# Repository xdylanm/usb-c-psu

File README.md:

# usb-c-psu
Notes for USB-C PSU design

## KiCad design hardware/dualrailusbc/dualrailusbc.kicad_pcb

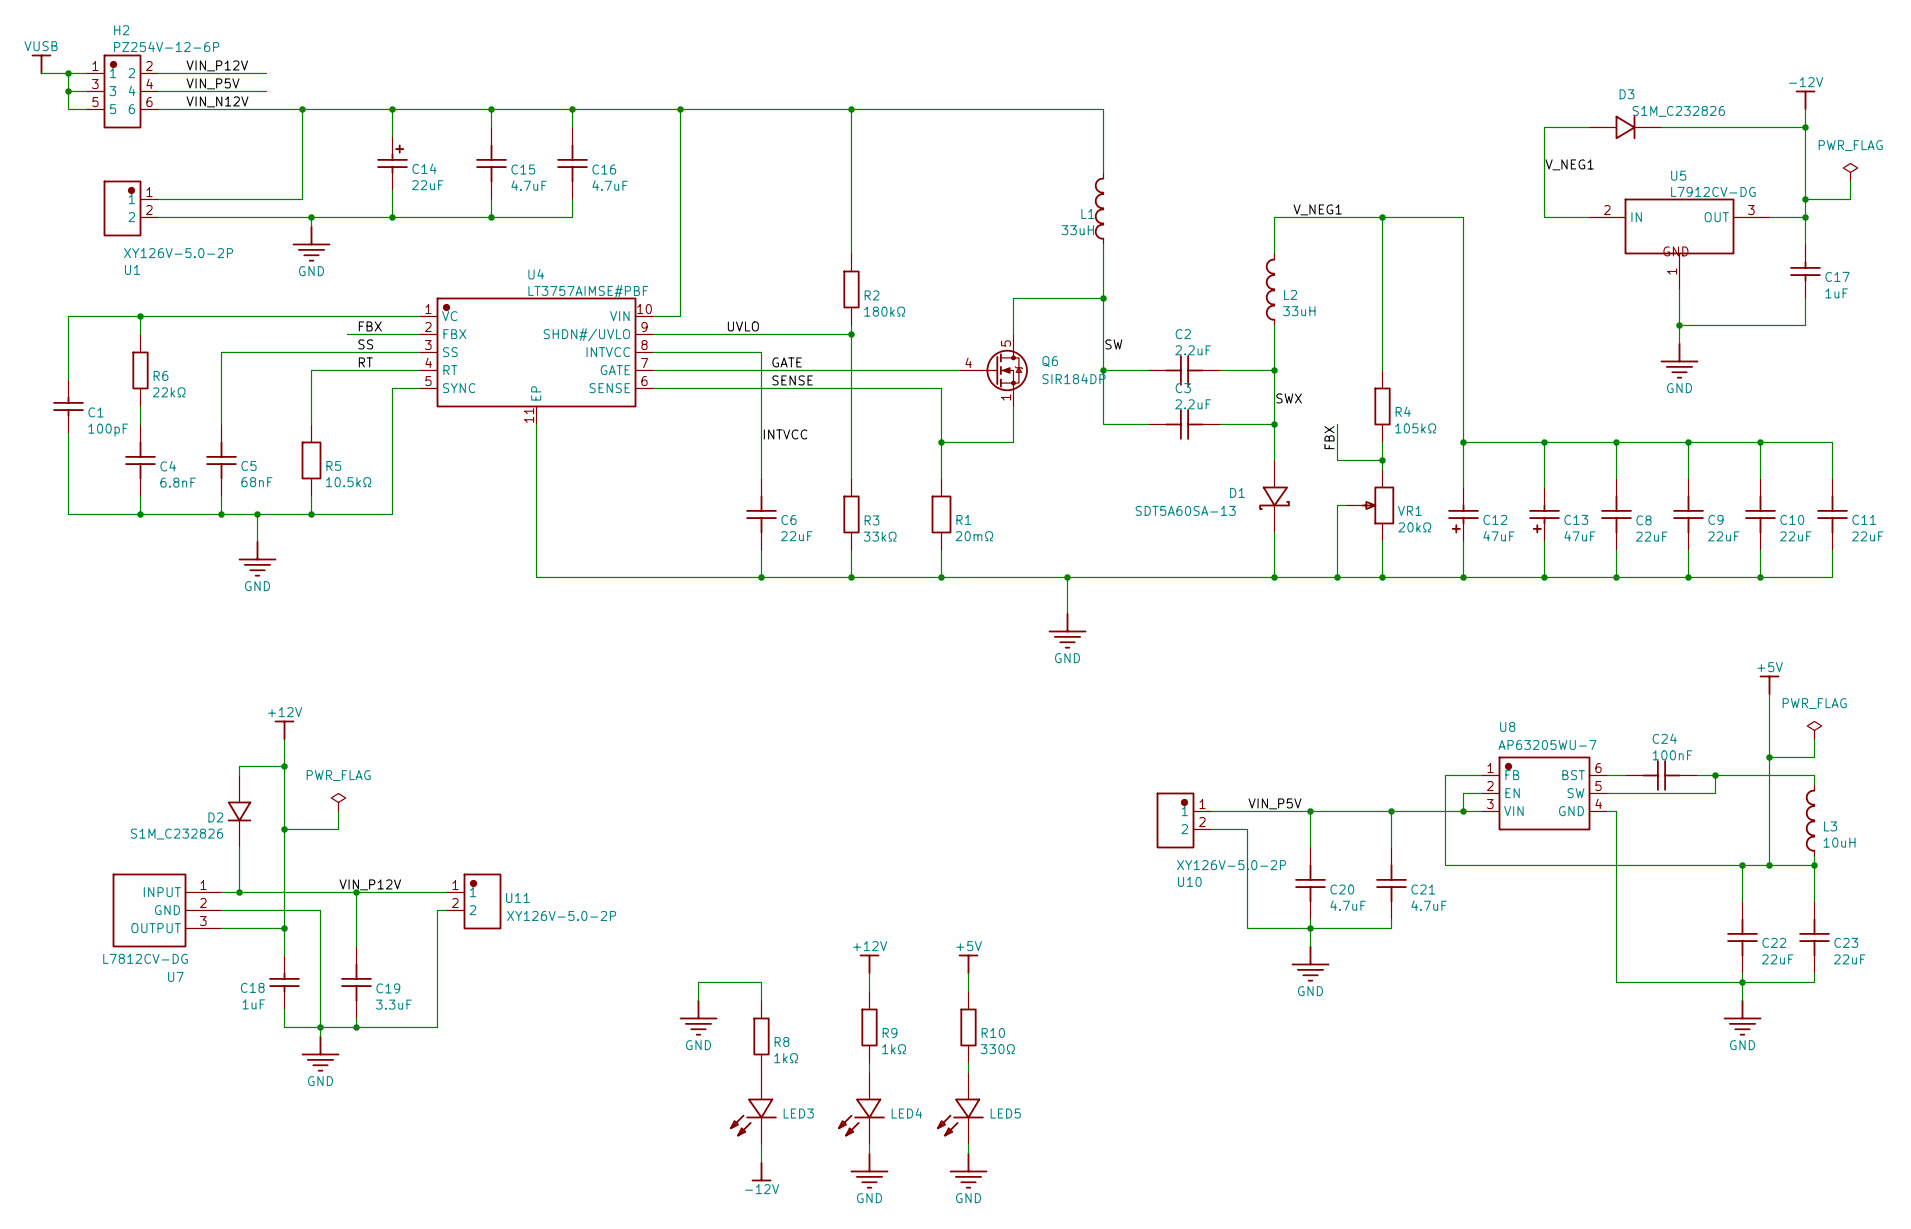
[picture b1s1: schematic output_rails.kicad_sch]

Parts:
C1: 100pF; C_0603_1608Metric; MANUFACTURER PART GRM1885C1H101JA01D; JLCPCB PART CLASS Extended Part
C2, C3: 2.2uF; C_1210_3225Metric; MANUFACTURER PART GRM32ER72A225KA35L; JLCPCB PART CLASS Extended Part
C4: 6.8nF; C_0603_1608Metric; MANUFACTURER PART GRM1885C1H682JA01D; JLCPCB PART CLASS Extended Part
C5: 68nF; C_0603_1608Metric; MANUFACTURER PART GCJ188R71H683KA12D; JLCPCB PART CLASS Extended Part
C6: 22uF; C_0603_1608Metric; MANUFACTURER PART GRM188R61A226ME15D; JLCPCB PART CLASS Extended Part
C8, C9, C10, C11: 22uF; C_1210_3225Metric; MANUFACTURER PART GRM32ER71E226KE15L; JLCPCB PART CLASS Extended Part
C12, C13: 47uF; CP_EIA-7343-30_AVX-N; MANUFACTURER PART TAJD476K025RNJ; JLCPCB PART CLASS Extended Part
C14: 22uF; CP_EIA-7343-30_AVX-N; MANUFACTURER PART TAJD226K035RNJ; JLCPCB PART CLASS Extended Part
C15, C16, C20, C21: 4.7uF; C_1210_3225Metric; MANUFACTURER PART GRM32ER71H475KA88L; JLCPCB PART CLASS Extended Part
C17, C18: 1uF; C_0805_2012Metric; MANUFACTURER PART GCM21BR71H105KA03L; JLCPCB PART CLASS Extended Part
C19: 3.3uF; C_1210_3225Metric; MANUFACTURER PART GRM32DR71H335KA88L; JLCPCB PART CLASS Extended Part
C22, C23: 22uF; C_0805_2012Metric; MANUFACTURER PART GRT21BR61C226ME13L; JLCPCB PART CLASS Extended Part
C24: 100nF; C_0603_1608Metric; MANUFACTURER PART GRM188R71H104KA93D; JLCPCB PART CLASS Extended Part
D1: SDT5A60SA-13; D_SMA; MANUFACTURER PART SDT5A60SA-13; JLCPCB PART CLASS Extended Part
D2, D3: S1M_C232826; D_SMA; MANUFACTURER PART S1M; JLCPCB PART CLASS Extended Part
H2: PZ254V-12-6P; PinHeader_2x03_P2.54mm_Vertical; MANUFACTURER PART PZ254V-12-6P; JLCPCB PART CLASS Extended Part
L1, L2: 33uH; L_SMD_Sumida_L11.5mm_W10.0mm; MANUFACTURER PART 104CDMCCDS-330MC; JLCPCB PART CLASS Extended Part
L3: 10uH; L_SMD_Sumida_L7.0mm_W6.6mm; MANUFACTURER PART 0624CDMCCDS-100MC
LED3, LED4, LED5: LTST-C150KGKT; LED_1206_3216Metric; MANUFACTURER PART LTST-C150KGKT; JLCPCB PART CLASS Extended Part
Q6: SIR184DP; PowerPAK_SO-8_Single
R1: 20mΩ; R_2512_6332Metric; MANUFACTURER PART PA2512FKE7W0R02E; JLCPCB PART CLASS Extended Part
R2: 180kΩ; R_0603_1608Metric; MANUFACTURER PART RC0603FR-07180KL; JLCPCB PART CLASS Extended Part
R3: 33kΩ; R_0603_1608Metric; MANUFACTURER PART RC0603FR-0733KL; JLCPCB PART CLASS Extended Part
R4: 105kΩ; R_0603_1608Metric; MANUFACTURER PART RC0603FR-07105KL; JLCPCB PART CLASS Extended Part
R5: 10.5kΩ; R_0603_1608Metric; MANUFACTURER PART RT0603DRD0710K5L; JLCPCB PART CLASS Extended Part
R6: 22kΩ; R_0603_1608Metric; MANUFACTURER PART RC0603FR-0722KL; JLCPCB PART CLASS Extended Part
R8, R9: 1kΩ; R_0603_1608Metric; MANUFACTURER PART RC0603FR-071KL; JLCPCB PART CLASS Extended Part
R10: 330Ω; R_0603_1608Metric; MANUFACTURER PART RC0603FR-07330RL; JLCPCB PART CLASS Extended Part
U1, U10, U11: XY126V-5.0-2P; TerminalBlock_Phoenix_MKDS-1,5-2_1x02_P5.00mm_Horizontal; MANUFACTURER PART XY126V-5.0-2P; JLCPCB PART CLASS Extended Part
U4: LT3757AIMSE#PBF; MSOP-10-1EP_3x3mm_P0.5mm_EP1.68x1.88mm; MANUFACTURER PART LT3757AIMSE#PBF
U5: L7912CV-DG; TO-220-3_Vertical; MANUFACTURER PART L7912CV-DG; JLCPCB PART CLASS Extended Part
U7: L7812CV-DG; TO-220-3_Vertical; MANUFACTURER PART L7812CV-DG; JLCPCB PART CLASS Extended Part
U8: AP63205WU-7; TSOT-23-6; MANUFACTURER PART AP63205WU-7; JLCPCB PART CLASS Extended Part
VR1: 20kΩ; Potentiometer_Bourns_3224W_Vertical; MANUFACTURER PART 3224W-1-203E; JLCPCB PART CLASS Extended Part

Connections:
+5V: C22.2, C23.2, L3.1, R10.2, U8.1 (FB); also elsewhere on the board
+12V: C18.2, D2.2 (A), R9.2, U7.3 (OUTPUT); also elsewhere on the board
-12V: C17.2, D3.1 (K), LED3.1 (K), U5.3 (OUT); also elsewhere on the board
/Output Rails/FBX: R4.1, U4.2 (FBX), VR1.1
/Output Rails/GATE: Q6.4 (G), U4.7 (GATE)
/Output Rails/INTVCC: C6.2, U4.8 (INTVCC)
/Output Rails/RT: R5.2, U4.4 (RT)
/Output Rails/SENSE: Q6.1 (S), Q6.2 (S), Q6.3 (S), R1.2, U4.6 (SENSE)
/Output Rails/SS: C5.2, U4.3 (SS)
/Output Rails/SW: C2.1, C3.1, L1.1, Q6.5 (D)
/Output Rails/SWX: C2.2, C3.2, D1.2, L2.1
/Output Rails/UVLO: R2.1, R3.2, U4.9 (SHDN#/UVLO)
/Output Rails/VIN_N12V: C14.1, C15.2, C16.2, H2.6, L1.2, R2.2, U1.1, U4.10 (VIN)
/Output Rails/VIN_P5V: C20.2, C21.2, H2.4, U8.2 (EN), U8.3 (VIN), U10.1
/Output Rails/VIN_P12V: C19.1, D2.1 (K), H2.2, U7.1 (INPUT), U11.1
/Output Rails/V_NEG1: C8.2, C9.2, C10.2, C11.2, C12.2, C13.2, D3.2 (A), L2.2, R4.2, U5.2 (IN)
GND: C1.1, C4.2, C5.1, C6.1, C8.1, C9.1, C10.1, C11.1, C12.1, C13.1, C14.2, C15.1, C16.1, C17.1, C18.1, C19.2, C20.1, C21.1, C22.1, C23.1, D1.1, LED4.1 (K), LED5.1 (K), R1.1, R3.1, R5.1, R8.2, U1.2, U4.5 (SYNC), U4.11 (EP), U5.1 (GND), U7.2 (GND), U8.4 (GND), U10.2, U11.2, VR1.2, VR1.3; also elsewhere on the board
unnamed: C4.1, R6.1
unnamed: LED3.2 (A), R8.1
unnamed: LED4.2 (A), R9.1
unnamed: LED5.2 (A), R10.1
unnamed: C1.2, R6.2, U4.1 (VC)
unnamed: C24.1, U8.6 (BST)
unnamed: C24.2, L3.2, U8.5 (SW)
VUSB: H2.1, H2.3, H2.5; also elsewhere on the board

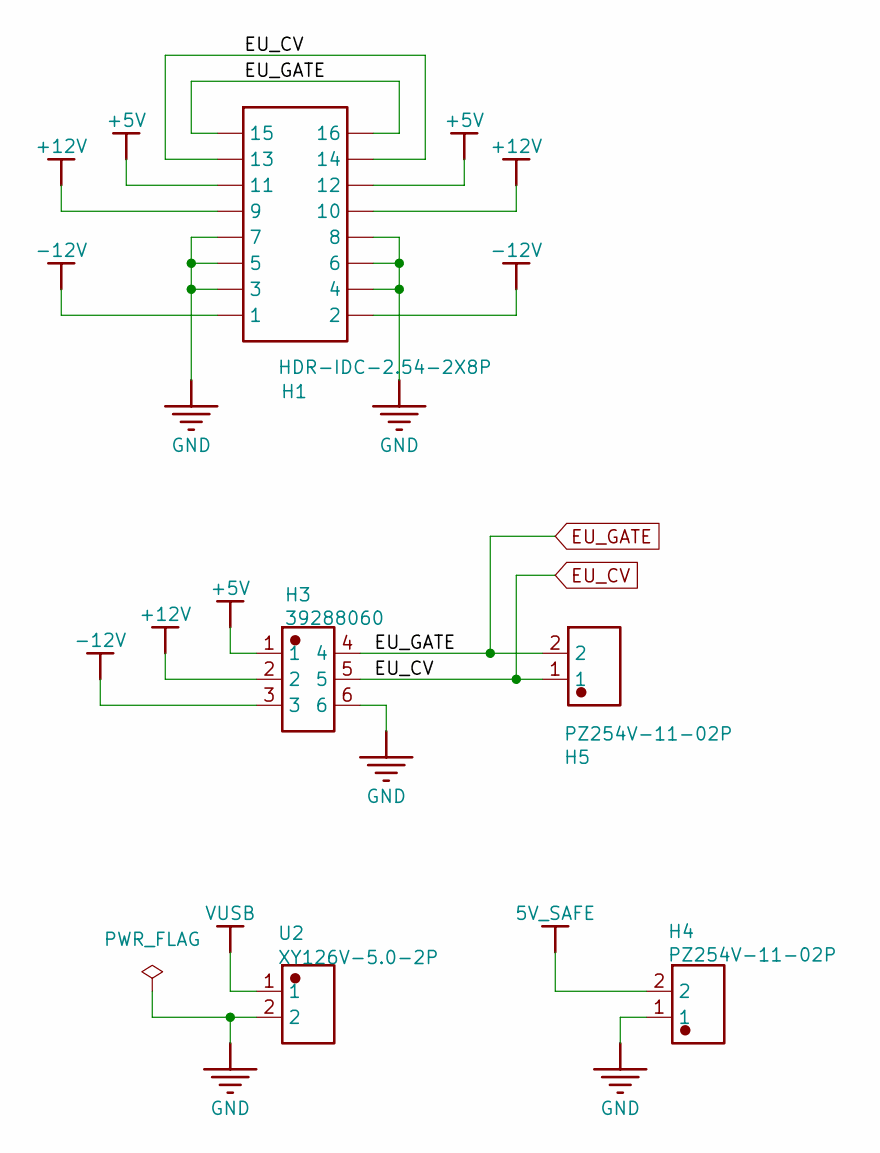
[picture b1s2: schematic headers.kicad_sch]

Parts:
H1: HDR-IDC-2.54-2X8P; IDC-Header_2x08_P2.54mm_Vertical; MANUFACTURER PART 2.54-2*8P简牛; JLCPCB PART CLASS Extended Part
H3: 39288060; Molex_Mini-Fit_Jr_5566-06A_2x03_P4.20mm_Vertical; MANUFACTURER PART 39288060; JLCPCB PART CLASS Extended Part
H4, H5: PZ254V-11-02P; PinHeader_2x01_P2.54mm_Vertical; MANUFACTURER PART PZ254V-11-02P; JLCPCB PART CLASS Extended Part
U2: XY126V-5.0-2P; TerminalBlock_Phoenix_MKDS-1,5-2_1x02_P5.00mm_Horizontal; MANUFACTURER PART XY126V-5.0-2P; JLCPCB PART CLASS Extended Part

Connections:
5V_SAFE: H4.2; also elsewhere on the board
+5V: H1.11, H1.12, H3.1; also elsewhere on the board
+12V: H1.9, H1.10, H3.2; also elsewhere on the board
-12V: H1.1, H1.2, H3.3; also elsewhere on the board
EU_CV: H1.13, H1.14, H3.5, H5.1
EU_GATE: H1.15, H1.16, H3.4, H5.2
GND: H1.3, H1.4, H1.5, H1.6, H1.7, H1.8, H3.6, H4.1, U2.2; also elsewhere on the board
VUSB: U2.1; also elsewhere on the board

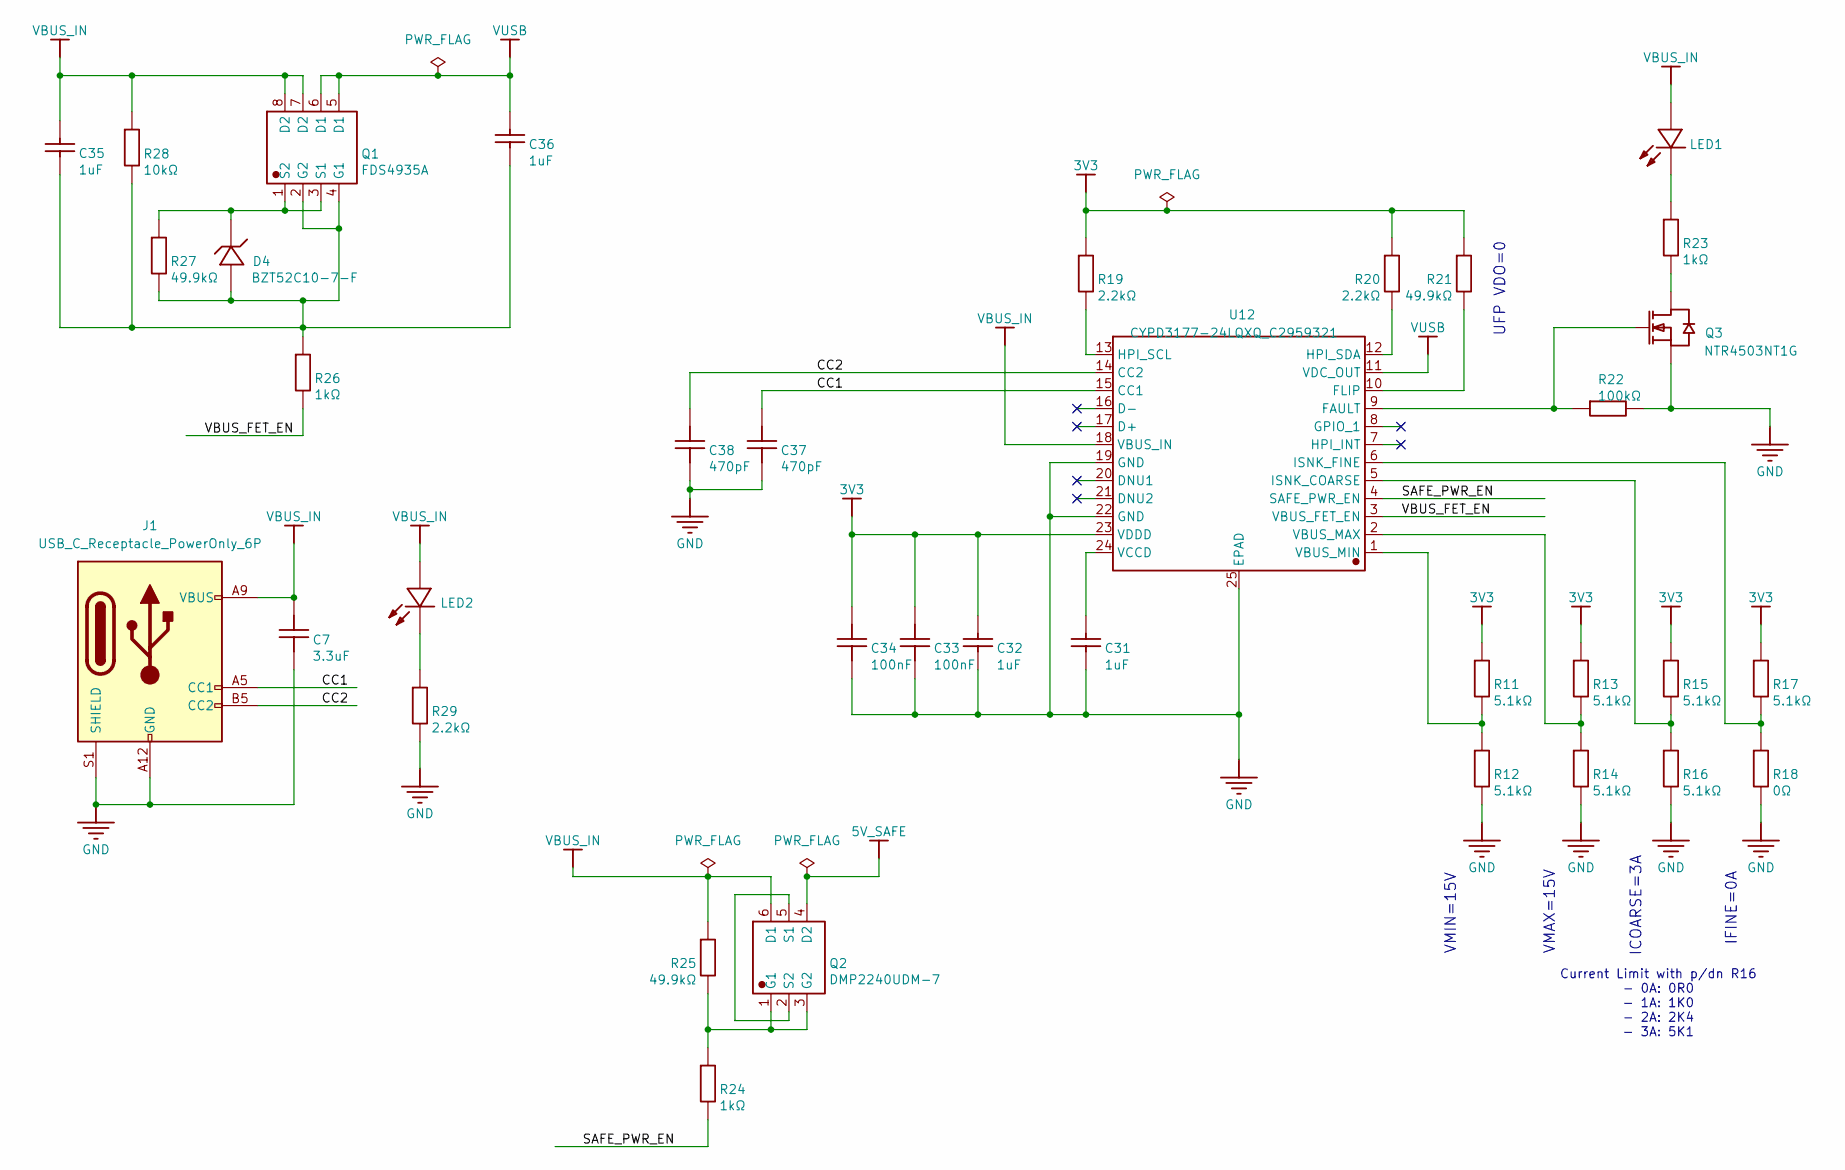
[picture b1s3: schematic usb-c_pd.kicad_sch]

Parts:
C7: 3.3uF; C_1210_3225Metric; MANUFACTURER PART GRM32DR71H335KA88L; JLCPCB PART CLASS Extended Part
C31, C32: 1uF; C_0603_1608Metric; MANUFACTURER PART GRM188R61H105KAALD; JLCPCB PART CLASS Extended Part
C33, C34: 100nF; C_0603_1608Metric; MANUFACTURER PART GRM188R71H104KA93D; JLCPCB PART CLASS Extended Part
C35, C36: 1uF; C_0805_2012Metric; MANUFACTURER PART GCM21BR71H105KA03L; JLCPCB PART CLASS Extended Part
C37, C38: 470pF; C_0603_1608Metric; MANUFACTURER PART GRM1885C1H471JA01D; JLCPCB PART CLASS Extended Part
D4: BZT52C10-7-F; D_SOD-123; MANUFACTURER PART BZT52C10-7-F; JLCPCB PART CLASS Extended Part
J1: USB_C_Receptacle_PowerOnly_6P; USB_C_Receptacle_GCT_USB4125-xx-x_6P_TopMnt_Horizontal
LED1: LTST-C150KRKT; LED_1206_3216Metric; MANUFACTURER PART LTST-C150KRKT; JLCPCB PART CLASS Extended Part
LED2: LTST-C150KGKT; LED_1206_3216Metric; MANUFACTURER PART LTST-C150KGKT; JLCPCB PART CLASS Extended Part
Q1: FDS4935A; SOIC-8_3.9x4.9mm_P1.27mm; MANUFACTURER PART FDS4935A
Q2: DMP2240UDM-7; SOT-23-6; MANUFACTURER PART DMP2240UDM-7; JLCPCB PART CLASS Extended Part
Q3: NTR4503NT1G; SOT-23-3; MANUFACTURER PART NTR4503NT1G; JLCPCB PART CLASS Extended Part
R11, R12, R13, R14, R15, R16, R17: 5.1kΩ; R_0603_1608Metric; MANUFACTURER PART RC0603FR-075K1L; JLCPCB PART CLASS Extended Part
R18: 0Ω; R_0603_1608Metric; MANUFACTURER PART RC0603JR-070RL; JLCPCB PART CLASS Extended Part
R19, R20, R29: 2.2kΩ; R_0603_1608Metric; MANUFACTURER PART RC0603JR-072K2L; JLCPCB PART CLASS Extended Part
R21, R25, R27: 49.9kΩ; R_0603_1608Metric; MANUFACTURER PART RC0603FR-0749K9L; JLCPCB PART CLASS Extended Part
R22: 100kΩ; R_0603_1608Metric; MANUFACTURER PART RC0603FR-07100KL; JLCPCB PART CLASS Extended Part
R23, R24, R26: 1kΩ; R_0603_1608Metric; MANUFACTURER PART RC0603FR-071KL; JLCPCB PART CLASS Extended Part
R28: 10kΩ; R_0603_1608Metric; MANUFACTURER PART RC0603FR-0710KL; JLCPCB PART CLASS Extended Part
U12: CYPD3177-24LQXQ_C2959321; TQFN-24_L4.0-W4.0-P0.50-TL-EP2.8; MANUFACTURER PART CYPD3177-24LQXQ; JLCPCB PART CLASS Extended Part

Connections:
3V3: C32.2, C33.2, C34.2, R11.2, R13.2, R15.2, R17.2, R19.2, R20.2, R21.2, U12.23 (VDDD)
5V_SAFE: Q2.4 (D2); also elsewhere on the board
/USB-C PD/CC1: C37.2, J1.A5 (CC1), U12.15 (CC1)
/USB-C PD/CC2: C38.2, J1.B5 (CC2), U12.14 (CC2)
/USB-C PD/SAFE_PWR_EN: R24.1, U12.4 (SAFE_PWR_EN)
/USB-C PD/VBUS_FET_EN: R26.1, U12.3 (VBUS_FET_EN)
GND: C7.2, C31.1, C32.1, C33.1, C34.1, C37.1, C38.1, J1.A12 (GND), J1.B12 (GND), J1.S1 (SHIELD), Q3.2 (S), R12.1, R14.1, R16.1, R18.1, R22.2, R29.1, U12.19 (GND), U12.22 (GND), U12.25 (EPAD); also elsewhere on the board
unnamed: C35.1, C36.1, D4.2 (A), Q1.2 (G2), Q1.4 (G1), R26.2, R27.1, R28.1
unnamed: D4.1 (C), Q1.1 (S2), Q1.3 (S1), R27.2
unnamed: LED1.1 (K), R23.2
unnamed: LED2.1 (K), R29.2
unnamed: Q2.1 (G1), Q2.3 (G2), R24.2, R25.1
unnamed: Q2.2 (S2), Q2.5 (S1)
unnamed: Q3.3 (D), R23.1
unnamed: Q3.1 (G), R22.1, U12.9 (FAULT)
unnamed: R21.1, U12.10 (FLIP)
unnamed: R19.1, U12.13 (HPI_SCL)
unnamed: R20.1, U12.12 (HPI_SDA)
unnamed: R15.1, R16.2, U12.5 (ISNK_COARSE)
unnamed: R17.1, R18.2, U12.6 (ISNK_FINE)
unnamed: R13.1, R14.2, U12.2 (VBUS_MAX)
unnamed: R11.1, R12.2, U12.1 (VBUS_MIN)
unnamed: C31.2, U12.24 (VCCD)
VBUS_IN: C7.1, C35.2, J1.A9 (VBUS), J1.B9 (VBUS), LED1.2 (A), LED2.2 (A), Q1.7 (D2), Q1.8 (D2), Q2.6 (D1), R25.2, R28.2, U12.18 (VBUS_IN)
VUSB: C36.2, Q1.5 (D1), Q1.6 (D1), U12.11 (VDC_OUT); also elsewhere on the board

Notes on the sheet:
ICOARSE=3A
VMAX=15V
IFINE=0A
Current Limit with p/dn R16 - 0A: 0R0 - 1A: 1K0 - 2A: 2K4 - 3A: 5K1
VMIN=15V
UFP VDO=0

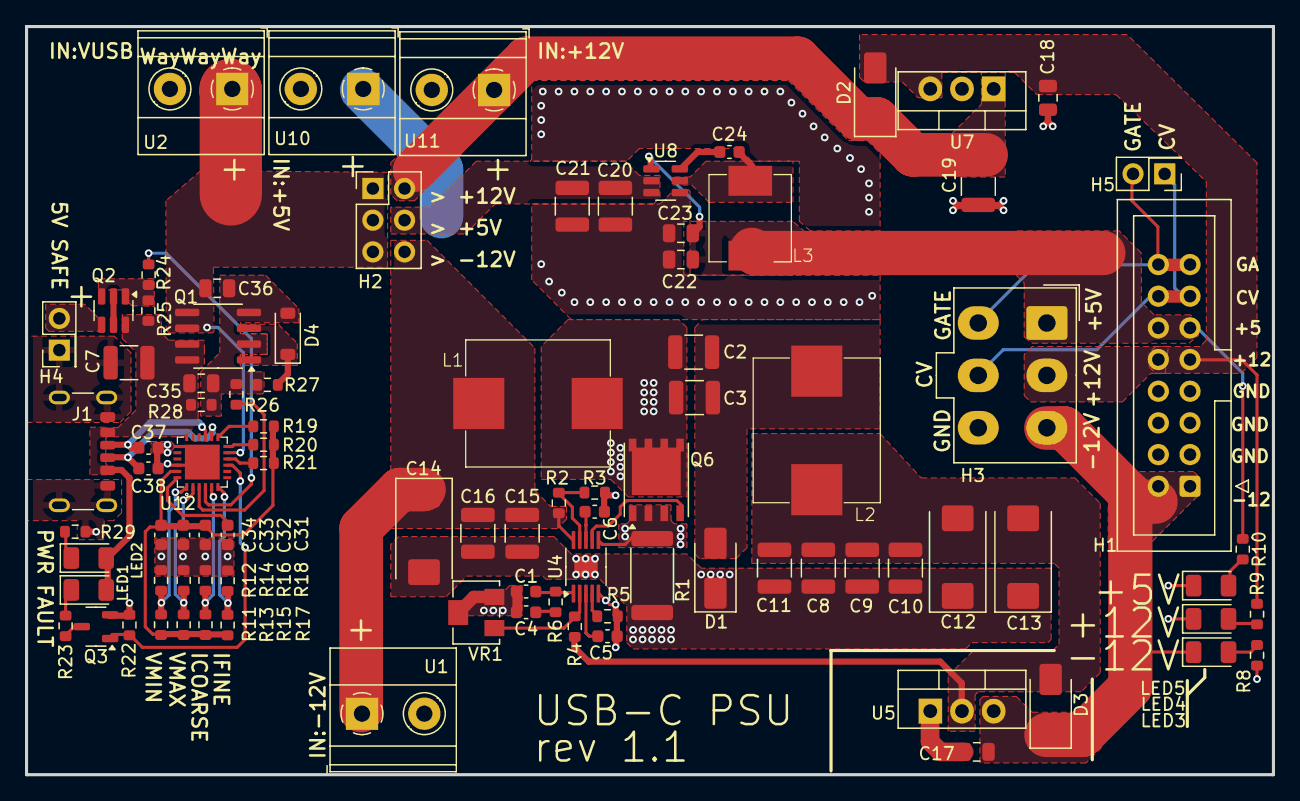
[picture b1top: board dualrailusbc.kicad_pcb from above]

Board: 2 copper layers, 100.0 x 60.0 mm, 92 parts (0 on the bottom side), 50 nets.

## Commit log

2024-03-02 initial design for the PSU
2024-06-20 Ported schematic and layout from EasyEDA to KiCAD. ERC & DRC OK, but had to modify some component symbols and add a few custom layouts
